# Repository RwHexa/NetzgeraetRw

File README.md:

# NetzgeraetRw — 12‑V‑Sperrwandler verstehen, prüfen & simulieren

Dokumentation eines isolierten **Sperrwandler‑Netzteils** (12 V, ~10–15 W) mit dem PWM‑Controller **OB2263**, Optokoppler **PC817** und **TL431** — aufbereitet als Lehr‑/Werkstattbericht in drei Schritten: **Verstehen → Prüfen → Simulieren**.

## 📚 Inhalt

| Teil | Datei | Inhalt |
|---|---|---|
| 🗂️ Start | [NetzgeraetUebersichtKi.md](NetzgeraetUebersichtKi.md) | Gesamtübersicht mit Inhaltsverzeichnis & Lernpfad |
| 📘 Verstehen | [NetzgeraetKi.md](NetzgeraetKi.md) | Funktionsanalyse (Regelung, Trafo, Bauteile) |
| 🔧 Prüfen | [NetzgeraetMessKi.md](NetzgeraetMessKi.md) | Störungs‑ & Fehleranalyse (sichere Messungen) |
| 🖥️ Simulieren | [NetzgeraetFalstadKi.md](NetzgeraetFalstadKi.md) | Aufbau im Falstad‑Browser |
| 🎛️ Interaktiv | [NetzgeraetSimulation.html](NetzgeraetSimulation.html) | Offline‑Simulation des Regelverhaltens |
| 📄 Heft | `NetzgeraetHeft.pdf` | Alles gebündelt als gestaltetes PDF‑Heft |

## 🎛️ Interaktive Simulation

`NetzgeraetSimulation.html` einfach im Browser öffnen (läuft offline, keine Installation). Schieberegler für **Netzspannung** und **Laststrom**, Knöpfe für **Lastsprung** und **Regelung öffnen** — zeigt live, wie der Regelkreis die 12 V hält und was bei offener Rückkopplung passiert.

## 🖼️ Diagramme

Alle selbst erstellten Diagramme liegen als `.svg` (Quelle) **und** `.png` (2×) vor:
`regelschleife` · `trafo_zwei_phasen` · `messablauf` · `vergleich_schaltplaene` · `projektkarte`.

## ⚖️ Rechte & Quellen

- **Eigene Inhalte** (Texte, selbst erstellte Diagramme, HTML‑Simulation, Heft, Logo): © Reinhard Wermeling (RwTec), erarbeitet mit Claude Code.
- ⚠️ **Fremde Bilder** (nur zu Lern‑/Referenzzwecken): einige Bitmap‑Schaltbilder und Fotos stammen aus dem Web und unterliegen fremdem Urheberrecht — u. a. `Schaltplan_vollstaendig.jpg` (Wasserzeichen ornatepixels.com), `Schaltplan.jpg` / `SchaltplanKl.JPG`, `PlatineKl.JPG`. **Nicht für Weiterverbreitung.** Vor einer etwaigen Veröffentlichung entfernen oder durch eigene Nachzeichnungen ersetzen.

---

*Werkstattbericht · RwTec · 2026 · erstellt mit Claude Code*

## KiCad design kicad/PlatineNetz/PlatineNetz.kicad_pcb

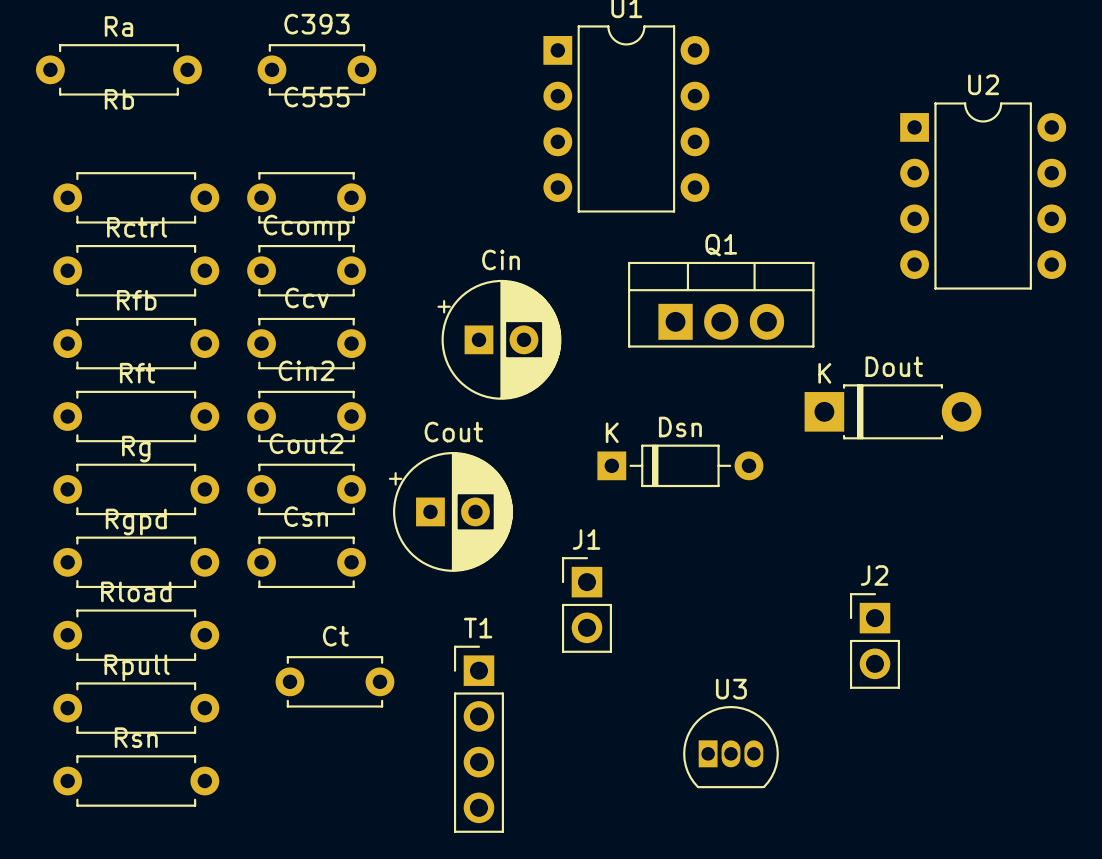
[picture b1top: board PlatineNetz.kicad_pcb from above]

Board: 2 copper layers, 29 parts (0 on the bottom side), 13 nets, no tracks yet.

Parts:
C393, C555: 100nF; C_Disc_D5.0mm_W2.5mm_P5.00mm
Ccomp: 10nF; C_Disc_D5.0mm_W2.5mm_P5.00mm
Ccv: 10nF; C_Disc_D5.0mm_W2.5mm_P5.00mm
Cin: 100uF/25V; CP_Radial_D6.3mm_P2.50mm
Cin2: 100nF; C_Disc_D5.0mm_W2.5mm_P5.00mm
Cout: 220uF/16V; CP_Radial_D6.3mm_P2.50mm
Cout2: 100nF; C_Disc_D5.0mm_W2.5mm_P5.00mm
Csn: 1nF; C_Disc_D5.0mm_W2.5mm_P5.00mm
Ct: 1nF; C_Disc_D5.0mm_W2.5mm_P5.00mm
Dout: 1N5819; D_DO-41_SOD81_P7.62mm_Horizontal
Dsn: 1N4148; D_DO-35_SOD27_P7.62mm_Horizontal
J1: 12V DC IN; PinHeader_1x02_P2.54mm_Vertical
J2: VOUT; PinHeader_1x02_P2.54mm_Vertical
Q1: IRLZ44N; TO-220-3_Vertical
Ra: 2k2; R_Axial_DIN0207_L6.3mm_D2.5mm_P7.62mm_Horizontal
Rb: 9k1; R_Axial_DIN0207_L6.3mm_D2.5mm_P7.62mm_Horizontal
Rctrl: 2k2; R_Axial_DIN0207_L6.3mm_D2.5mm_P7.62mm_Horizontal
Rfb: 10k; R_Axial_DIN0207_L6.3mm_D2.5mm_P7.62mm_Horizontal
Rft: 10k; R_Axial_DIN0207_L6.3mm_D2.5mm_P7.62mm_Horizontal
Rg: 22; R_Axial_DIN0207_L6.3mm_D2.5mm_P7.62mm_Horizontal
Rgpd: 10k; R_Axial_DIN0207_L6.3mm_D2.5mm_P7.62mm_Horizontal
Rload: 25; R_Axial_DIN0207_L6.3mm_D2.5mm_P7.62mm_Horizontal
Rpull: 4k7; R_Axial_DIN0207_L6.3mm_D2.5mm_P7.62mm_Horizontal
Rsn: 100; R_Axial_DIN0207_L6.3mm_D2.5mm_P7.62mm_Horizontal
T1: EE16, Np:Ns=2:1; PinHeader_1x04_P2.54mm_Vertical
U1: NE555; DIP-8_W7.62mm
U2: LM393; DIP-8_W7.62mm
U3: TL431; TO-92_Inline

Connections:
CLAMP: Csn.1, Dsn.1, Rsn.1
COMPOUT: Rg.1, Rpull.2, U2.1
CONTROL: Ccomp.1, Rctrl.2, U2.3, U3.3
DRAIN: Dsn.2, Q1.2, T1.1
FB: Ccomp.2, Rfb.1, Rft.2, U3.1
GATE: Q1.1, Rg.2, Rgpd.1
GND: C393.2, C555.2, Ccv.2, Cin.2, Cin2.2, Cout.2, Cout2.2, Ct.2, J1.2, J2.2, Q1.3, Rfb.2, Rgpd.2, Rload.2, T1.4, U1.1, U2.4, U2.5, U3.2
unnamed: Ra.2, Rb.1, U1.7
unnamed: Ccv.1, U1.5
RAMP: Ct.1, Rb.2, U1.2, U1.6, U2.2
SEC: Dout.2, T1.3
VIN: C393.1, C555.1, Cin.1, Cin2.1, Csn.2, J1.1, Ra.1, Rctrl.1, Rpull.1, Rsn.2, T1.2, U1.4, U1.8, U2.6, U2.8
VOUT: Cout.1, Cout2.1, Dout.1, J2.1, Rft.1, Rload.1
